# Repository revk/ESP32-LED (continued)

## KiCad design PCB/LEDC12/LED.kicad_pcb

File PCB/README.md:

# PCBs

Various PCBs designed for use with LED code.

## Trademark

This is an open source project, but bear in mind you cannot sell boards bearing the Andrews & Arnold Ltd name, the A&A logo, the registered trademark AJK logo, or the GS1 allocated EANs assigned to Andrews & Arnold Ltd.

## Coaster

Coaster board

## LEDA

USB-A board

## LEDC

USB-C board

## LEDX

Non USB board

## LEDR

USB-C uber board

## LEDx2

USB-C dual LED board

## LED32

88 LED disk, 32mm diameter

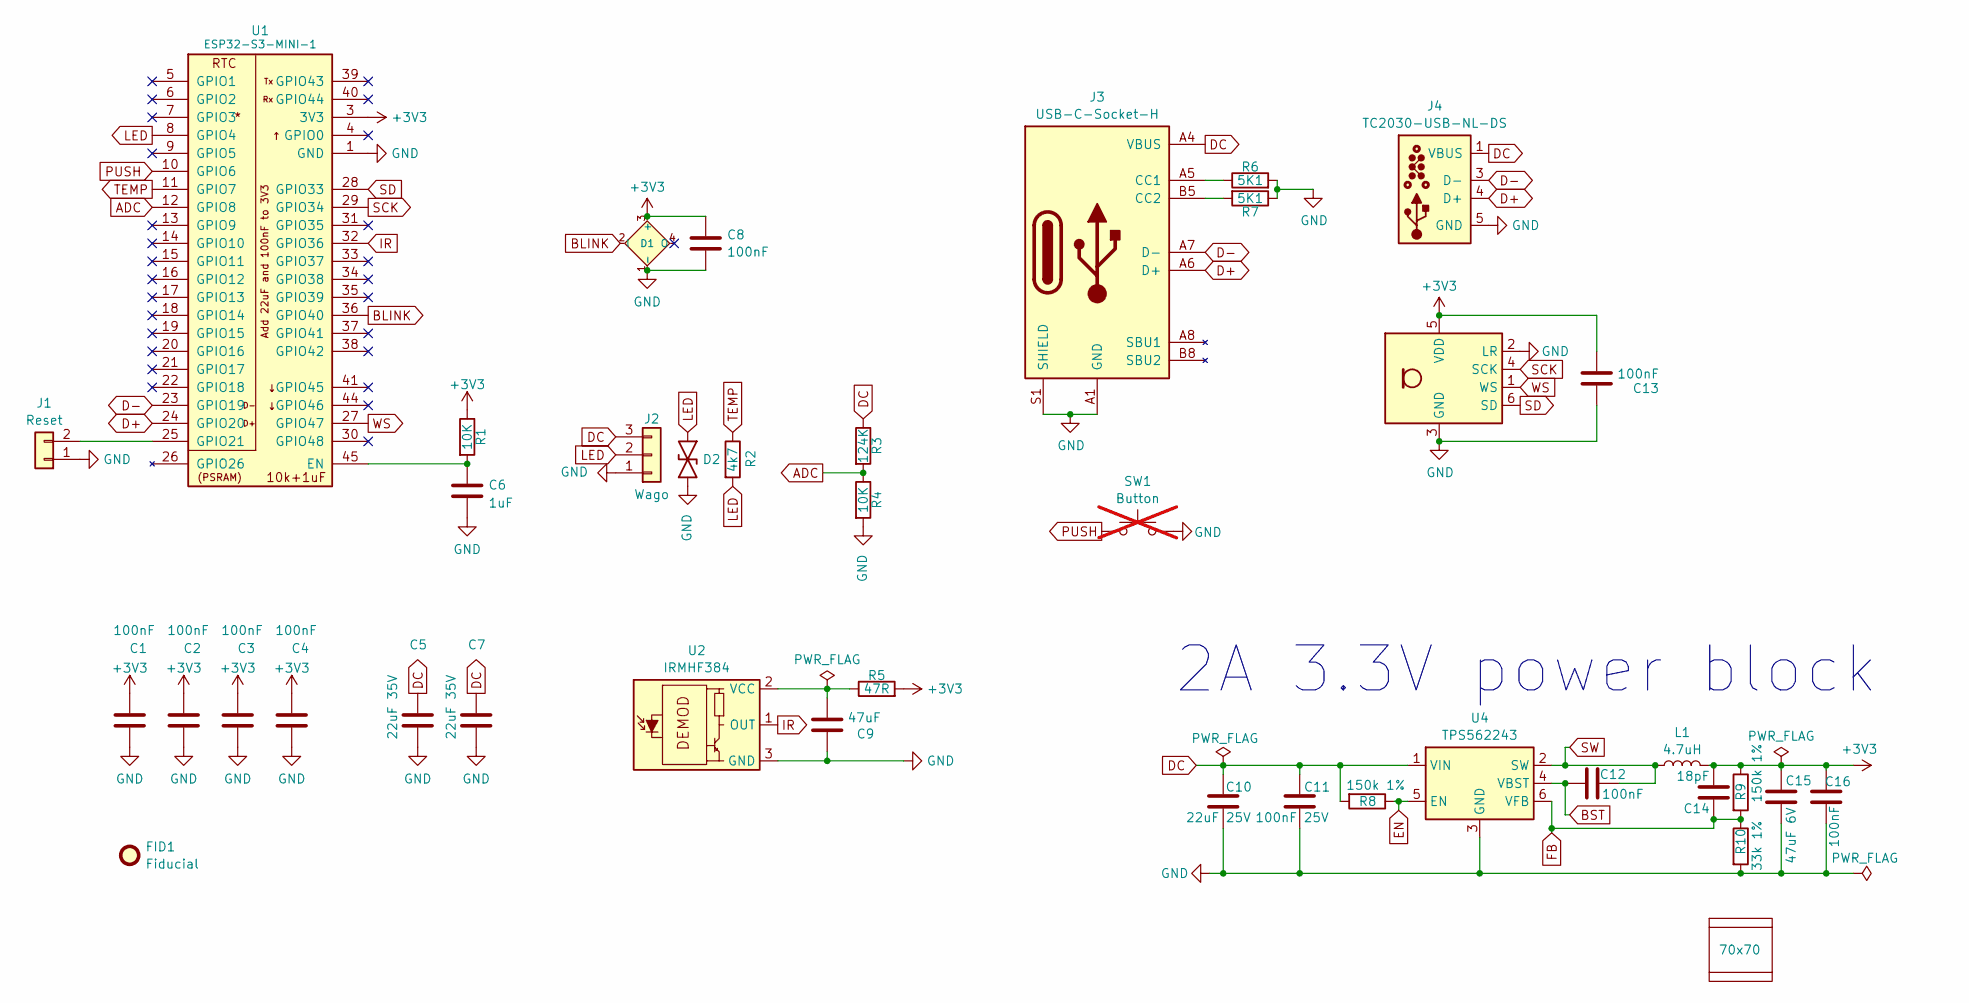
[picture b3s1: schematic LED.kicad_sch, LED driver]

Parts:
C1, C2, C3, C4, C8, C13: 100nF; C_0201
C5, C7: 22uF 35V; C_0805; MPN C6119901
C6: 1uF; C_0201
C9: 47uF; C_0603
C10: 22uF 25V; C_0805; MPN C45783
C11: 100nF 25V; C_0402; MPN C56392
C12, C16: 100nF; C_0201; MPN C76934
C14: 18pF; C_0201; MPN C62164
C15: 47uF 6V; C_0805; MPN C16780
D1: XL-1010RGBC-WS2812B; SMD1615; MPN C5349954
D2: DFN1006-2L; MPN C5137770
FID1: Fiducial; Fiducial_1mm_Mask2mm
J1: Reset; AA-Pad
J2: Wago; WAGO-2060-453-998-404; MPN C2765056
J3: USB-C-Socket-H; MPN C709357
J4: TC2030-USB-NL-DS; Tag-Connect_TC2030-IDC-NL_2x03_P1.27mm_Vertical
L1: 4.7uH; L_5x5; MPN C307876
PCB1: 70x70; PCB7070
R1, R4: 10K; R_0201; MPN C473048
R2: 4k7; R_0201; MPN C270346
R3: 124K; R_0201; MPN C423759
R5: 47R; R_0201; MPN C273279
R6, R7: 5K1; R_0201; MPN C274341
R8, R9: 150k 1%; R_0201; MPN C310173
R10: 33k 1%; R_0201; MPN C320835
SW1: Button; SW_Push_1P1T_NO_6x6mm; not fitted
U1: ESP32-S3-MINI-1; MPN C3013941
U2: IRMHF384; IR-SMD-4P,3.35x3.9mm; MPN C7280961
U3: ICS43434_MEMS_Mic; ICS43434_MEMS_Mic_Open; MPN C5656610
U4: TPS562243; SOT-563; MPN C42295941
V1, V2: VCUT70N

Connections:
+3V3: C1.1, C2.1, C3.1, C4.1, C8.1, C13.2, C14.2, C15.1, C16.2, D1.3 (+), L1.2, R1.1, R5.2, R9.1, U1.3 (3V3), U3.5 (VDD)
ADC: R3.2, R4.1, U1.12 (GPIO8)
BLINK: D1.2 (I), U1.36 (GPIO40)
BST: C12.1, U4.4 (VBST)
D+: J3.A6 (D+), J3.B6 (D+), J4.4 (D+), U1.24 (GPIO20)
D-: J3.A7 (D-), J3.B7 (D-), J4.2 (NC), J4.3 (D-), J4.6 (NC), U1.23 (GPIO19)
DC: C5.1, C7.1, C10.1, C11.1, J2.3, J3.A4 (VBUS), J3.A9 (VBUS), J3.B4 (VBUS), J3.B9 (VBUS), J4.1 (VBUS), R3.1, R8.2, U4.1 (VIN)
EN: R8.1, U4.5 (EN)
FB: C14.1, R9.2, R10.1, U4.6 (VFB)
GND: C1.2, C2.2, C3.2, C4.2, C5.2, C6.2, C7.2, C8.2, C9.2, C10.2, C11.2, C13.1, C15.2, C16.1, D1.1 (-), D2.1, J1.1, J2.1, J3.A1 (GND), J3.A12 (GND), J3.B1 (GND), J3.B12 (GND), J3.S1 (SHIELD), J4.5 (GND), R4.2, R6.2, R7.1, R10.2, SW1.2, U1.1 (GND), U1.2 (GND), U1.42 (GND), U1.43 (GND), U1.46 (GND), U1.47 (GND), U1.48 (GND), U1.49 (GND), U1.50 (GND), U1.51 (GND), U1.52 (GND), U1.53 (GND), U1.54 (GND), U1.55 (GND), U1.56 (GND), U1.57 (GND), U1.58 (GND), U1.59 (GND), U1.60 (GND), U1.61 (GND), U1.62 (GND), U1.63 (GND), U1.64 (GND), U1.65 (GND), U2.3 (GND), U2.4 (GND), U3.2 (LR), U3.3 (GND), U4.3 (GND)
IR: U1.32 (GPIO36), U2.1 (OUT)
LED: D2.2, J2.2, R2.2, U1.8 (GPIO4)
unnamed: J1.2, U1.25 (GPIO21)
unnamed: J3.A5 (CC1), R6.1
unnamed: J3.B5 (CC2), R7.2
unnamed: C6.1, R1.2, U1.45 (EN)
unnamed: C9.1, R5.1, U2.2 (VCC)
PUSH: SW1.1, U1.10 (GPIO6)
SCK: U1.29 (GPIO34), U3.4 (SCK)
SD: U1.28 (GPIO33), U3.6 (SD)
SW: C12.2, L1.1, U4.2 (SW)
TEMP: R2.1, U1.11 (GPIO7)
WS: U1.27 (GPIO47), U3.1 (WS)

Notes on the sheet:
2A 3.3V power block

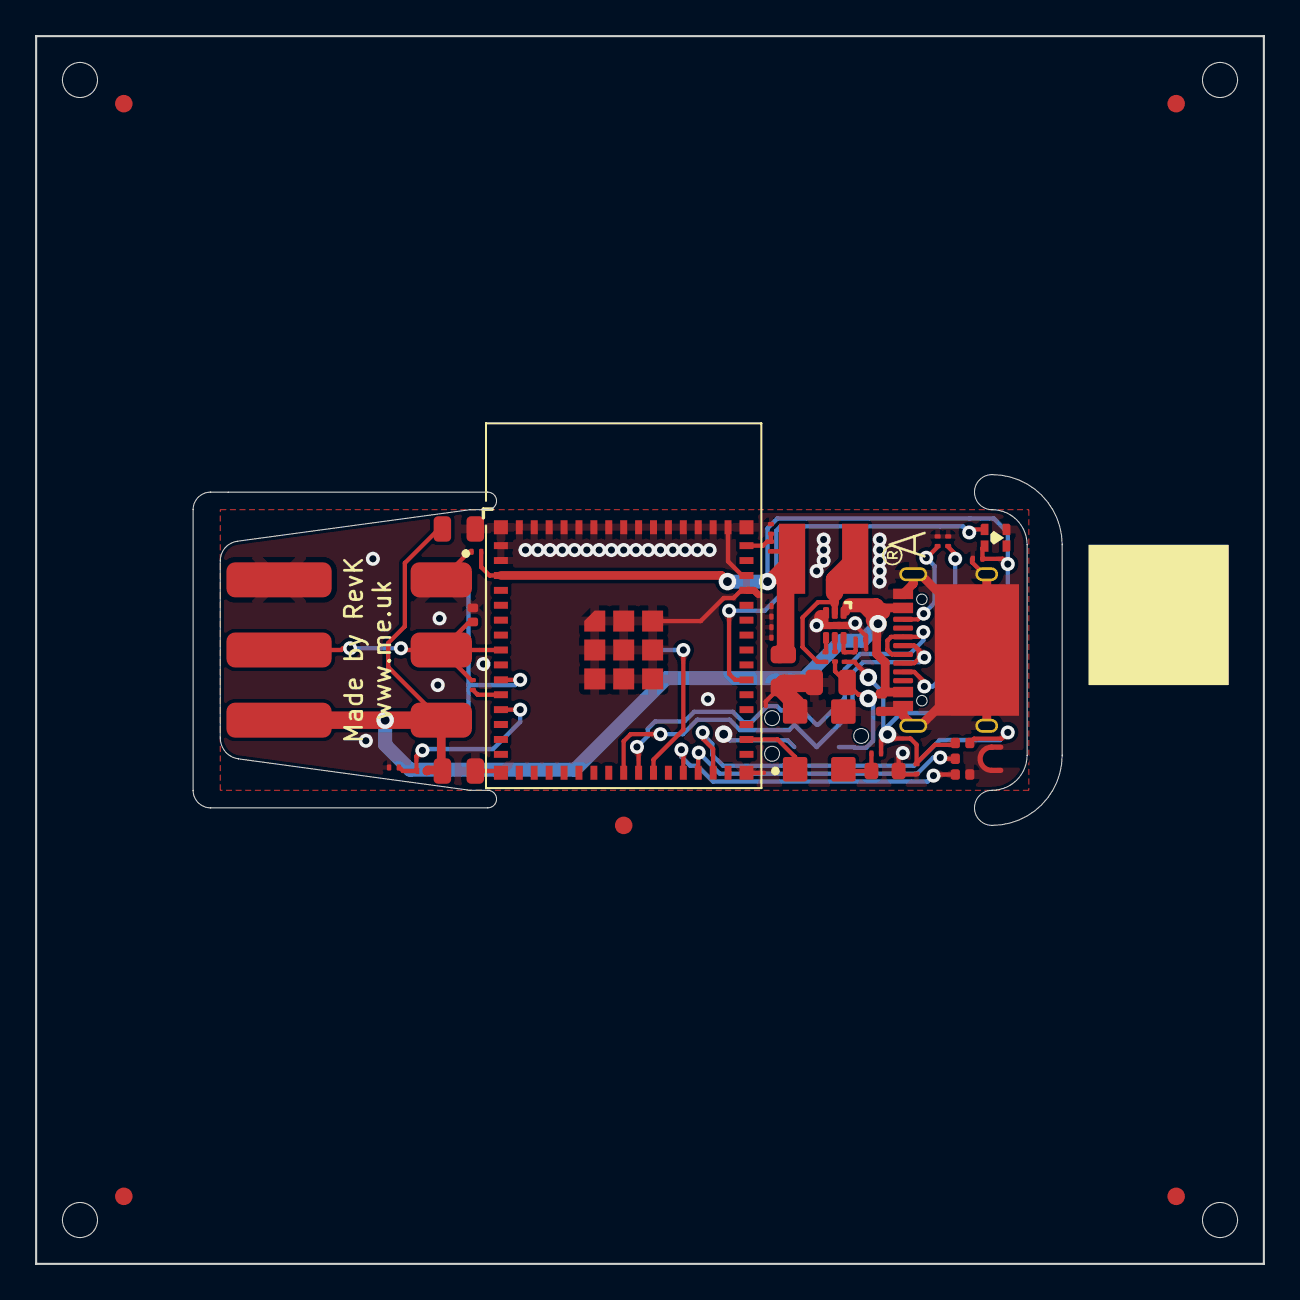
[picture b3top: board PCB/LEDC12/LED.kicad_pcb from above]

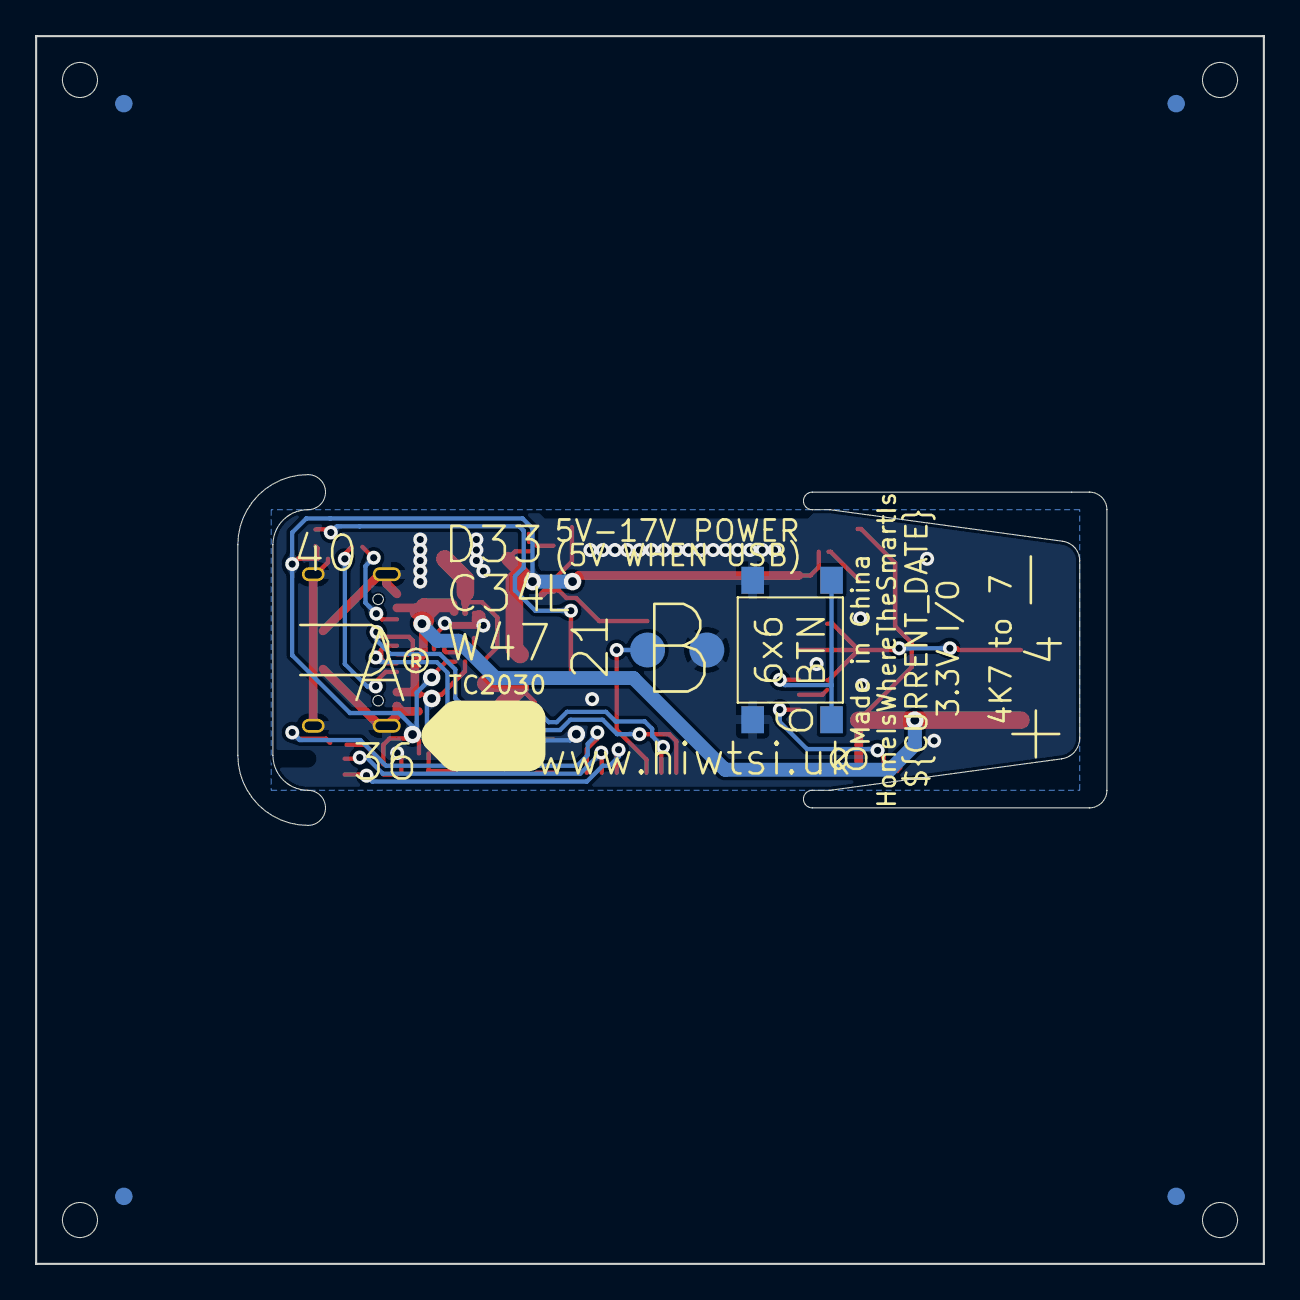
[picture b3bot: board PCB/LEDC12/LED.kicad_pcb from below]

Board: 2 copper layers, 70.0 x 70.0 mm, 42 parts (3 on the bottom side), 23 nets.

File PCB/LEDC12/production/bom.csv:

Designator,Footprint,Quantity,Value,LCSC Part #
"C1, C13, C2, C3, C4, C8",C_0201,6,100nF,
C10,C_0805,1,22uF 25V,C45783
C11,C_0402,1,100nF 25V,C56392
"C12, C16",C_0201,2,100nF,C76934
C14,C_0201,1,18pF,C62164
C15,C_0805,1,47uF 6V,C16780
"C5, C7",C_0805,2,22uF 35V,C6119901
C6,C_0201,1,1uF,
C9,C_0603,1,47uF,
D1,SMD1615,1,XL-1010RGBC-WS2812B,C5349954
D2,DFN1006-2L,1,~,C5137770
J2,WAGO-2060-453-998-404,1,Wago,C2765056
J3,USB-C-Socket-H,1,USB-C-Socket-H,C709357
L1,L_5x5,1,4.7uH,C307876
"R1, R4",R_0201,2,10K,C473048
R10,R_0201,1,33k 1%,C320835
R2,R_0201,1,4k7,C270346
R3,R_0201,1,124K,C423759
R5,R_0201,1,47R,C273279
"R6, R7",R_0201,2,5K1,C274341
"R8, R9",R_0201,2,150k 1%,C310173
U1,ESP32-S3-MINI-1,1,ESP32-S3-MINI-1-N4R2,C3013941
U2,"IR-SMD-4P,3.35x3.9mm",1,IRMHF384,C7280961
U3,ICS43434_MEMS_Mic_Open,1,ICS43434_MEMS_Mic,C5656610
U4,SOT-563,1,TPS562243,C42295941

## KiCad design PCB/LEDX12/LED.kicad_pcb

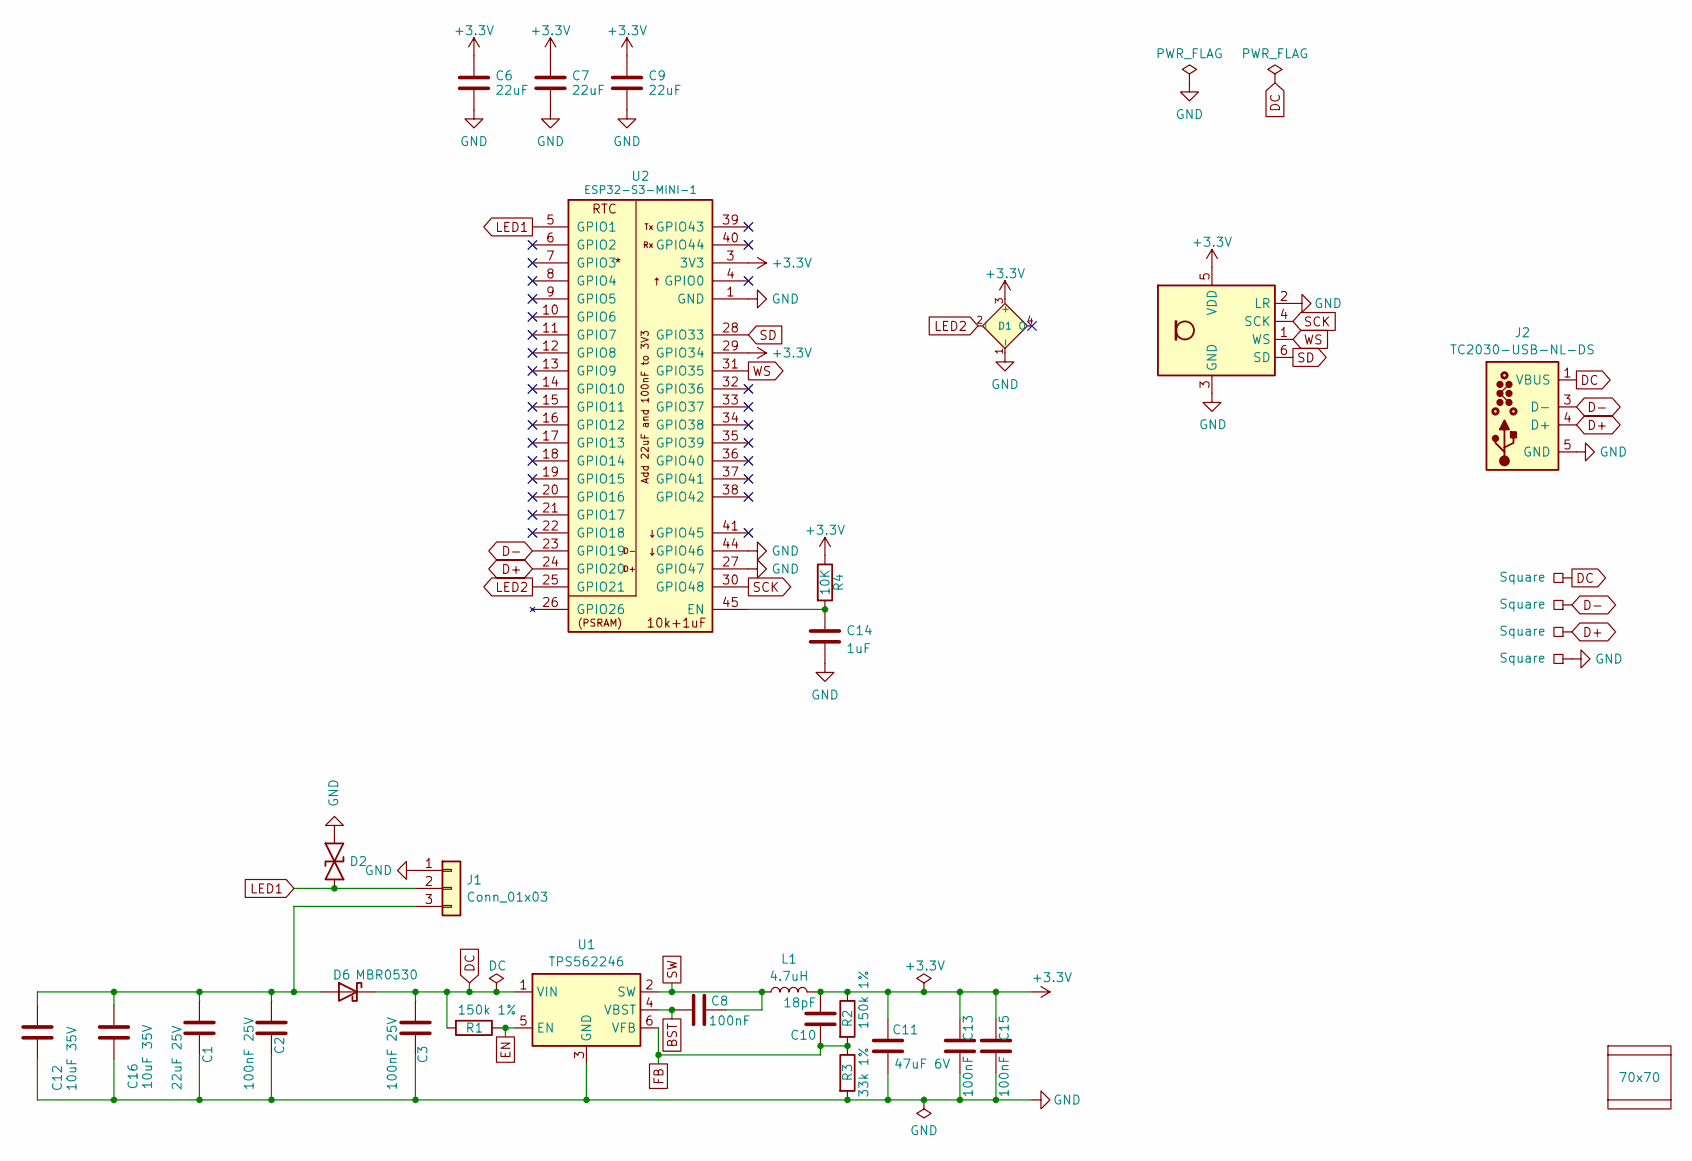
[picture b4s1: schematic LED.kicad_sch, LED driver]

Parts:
C1: 22uF 25V; C_0805; MPN C45783
C2, C3: 100nF 25V; C_0402; MPN C56392
C6, C7, C9: 22uF; C_0402
C8, C13, C15: 100nF; C_0201; MPN C76934
C10: 18pF; C_0201; MPN C62164
C11: 47uF 6V; C_0805; MPN C16780
C12, C16: 10uF 35V; C_0603; MPN C194427
C14: 1uF; C_0201
D1: XL-1010RGBC-WS2812B; SMD1615; MPN C5349954
D2: DFN1006-2L; MPN C5137770
D6: MBR0530; D_SOD-123; MPN C5204746
J1: Conn_01x03; WAGO-2060-453-998-404-O; MPN C2765056
J2: TC2030-USB-NL-DS; Tag-Connect_TC2030-IDC-NL_2x03_P1.27mm_Vertical
L1: 4.7uH; L_5x5; MPN C307876
P1, P2, P3, P4: Square; PAD-2mm
PCB1: 70x70; PCB7070
R1, R2: 150k 1%; R_0201; MPN C310173
R3: 33k 1%; R_0201; MPN C320835
R4: 10K; R_0201; MPN C473048
U1: TPS562246; SOT-563; MPN C41833479
U2: ESP32-S3-MINI-1; MPN C3013941
U3: ICS43434_MEMS_Mic; ICS43434_MEMS_Mic_Open; MPN C5656610
V1, V2: 70; VCUT70N

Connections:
+3.3V: C6.1, C7.1, C9.1, C10.2, C11.1, C13.2, C15.2, D1.3 (+), L1.2, R2.1, R4.1, U2.3 (3V3), U2.29 (GPIO34), U3.5 (VDD)
BST: C8.1, U1.4 (VBST)
D+: J2.4 (D+), P3.1, U2.24 (GPIO20)
D-: J2.2 (NC), J2.3 (D-), J2.6 (NC), P2.1, U2.23 (GPIO19)
DC: C3.1, D6.1 (K), J2.1 (VBUS), P1.1, R1.2, U1.1 (VIN)
EN: R1.1, U1.5 (EN)
FB: C10.1, R2.2, R3.1, U1.6 (VFB)
GND: C1.2, C2.2, C3.2, C6.2, C7.2, C9.2, C11.2, C12.2, C13.1, C14.2, C15.1, C16.2, D1.1 (-), D2.1, J1.1, J2.5 (GND), P4.1, R3.2, U1.3 (GND), U2.1 (GND), U2.2 (GND), U2.27 (GPIO47), U2.42 (GND), U2.43 (GND), U2.44 (GPIO46), U2.46 (GND), U2.47 (GND), U2.48 (GND), U2.49 (GND), U2.50 (GND), U2.51 (GND), U2.52 (GND), U2.53 (GND), U2.54 (GND), U2.55 (GND), U2.56 (GND), U2.57 (GND), U2.58 (GND), U2.59 (GND), U2.60 (GND), U2.61 (GND), U2.62 (GND), U2.63 (GND), U2.64 (GND), U2.65 (GND), U3.2 (LR), U3.3 (GND)
LED1: D2.2, J1.2, U2.5 (GPIO1)
LED2: D1.2 (I), U2.25 (GPIO21)
unnamed: C1.1, C2.1, C12.1, C16.1, D6.2 (A), J1.3
unnamed: C14.1, R4.2, U2.45 (EN)
SCK: U2.30 (GPIO48), U3.4 (SCK)
SD: U2.28 (GPIO33), U3.6 (SD)
SW: C8.2, L1.1, U1.2 (SW)
WS: U2.31 (GPIO35), U3.1 (WS)

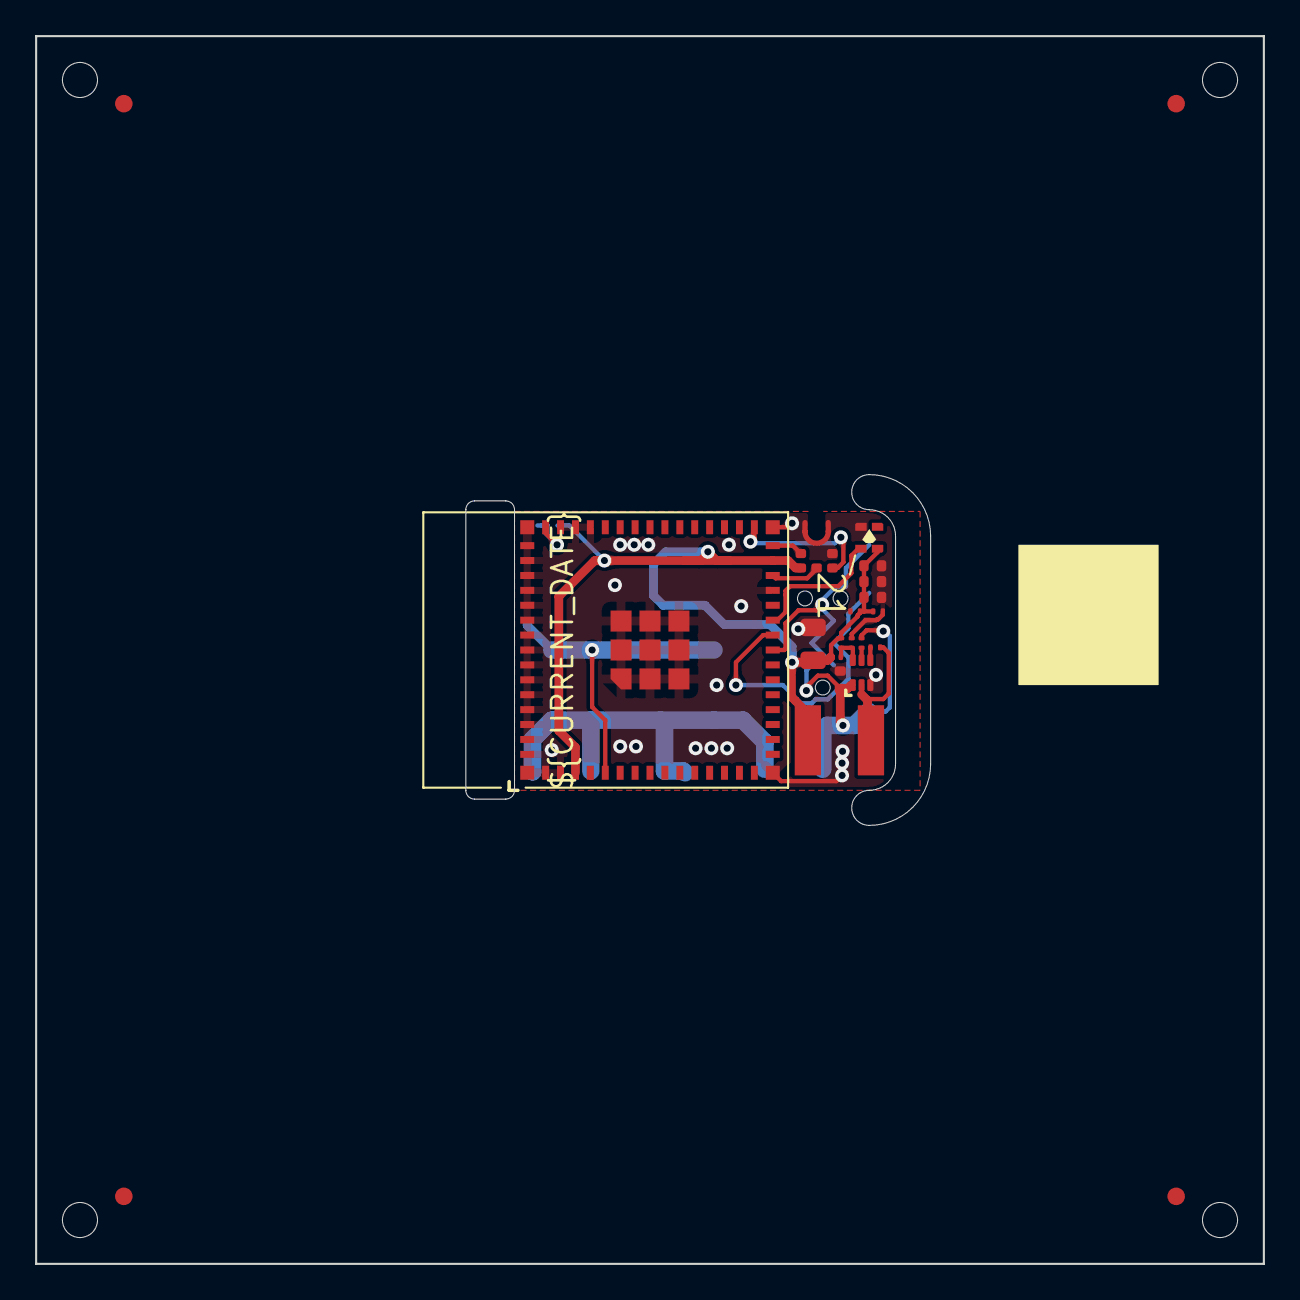
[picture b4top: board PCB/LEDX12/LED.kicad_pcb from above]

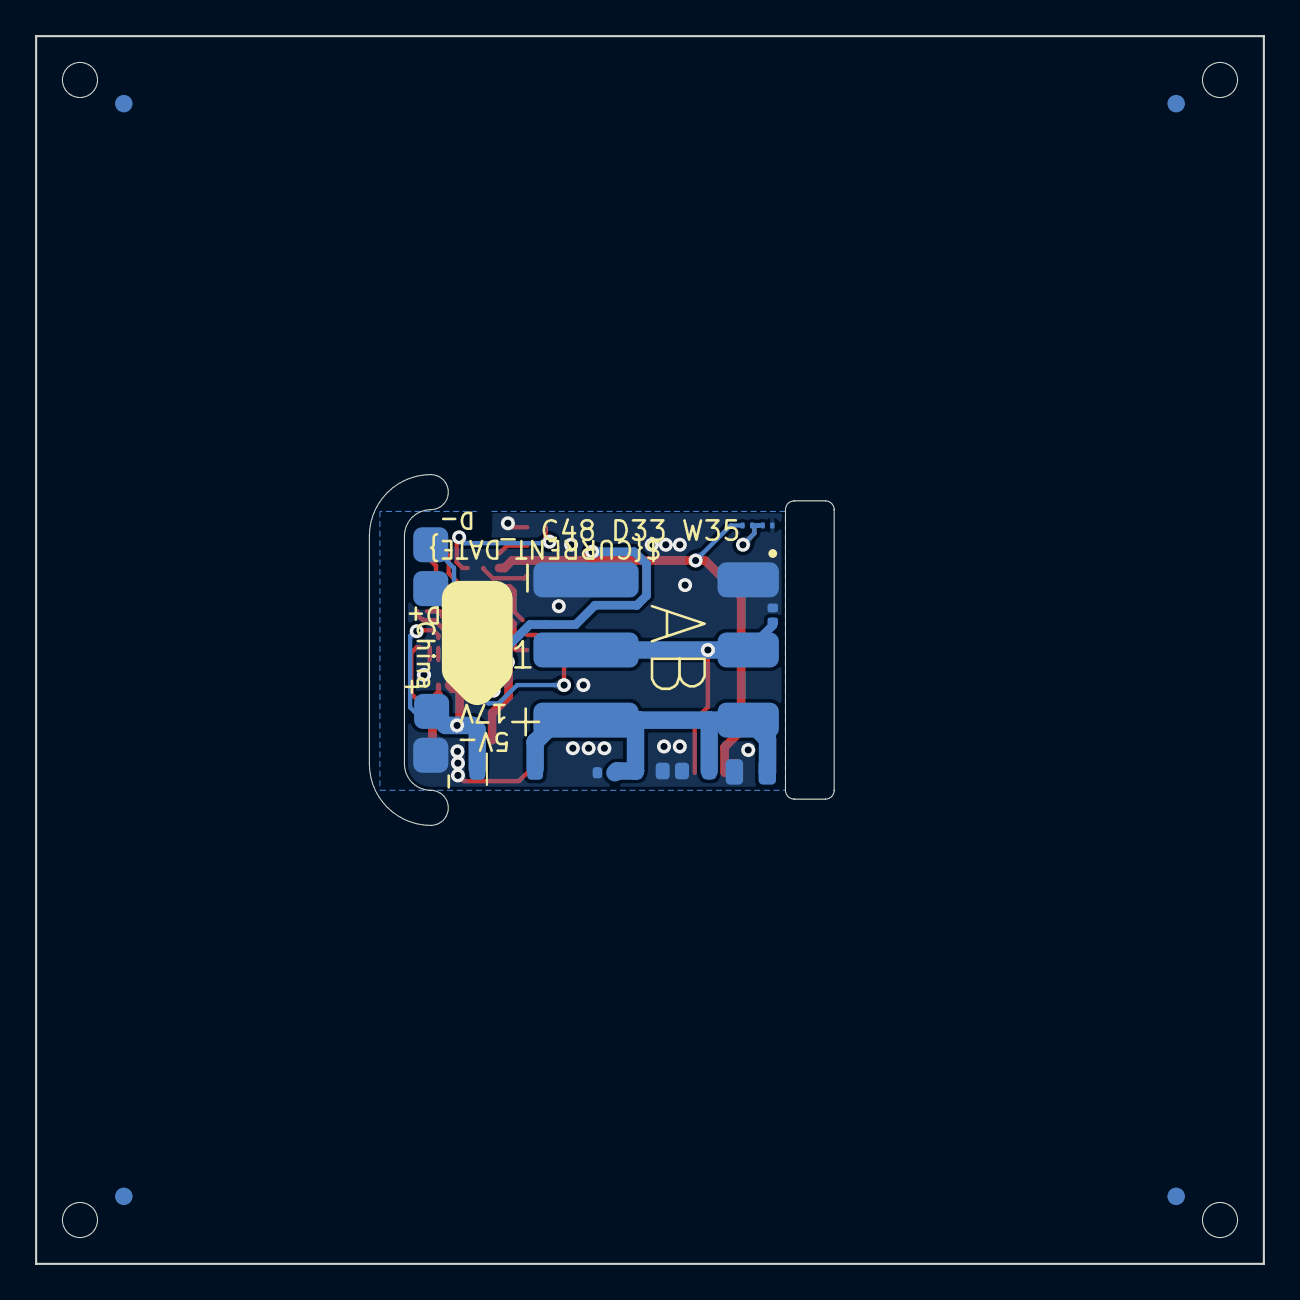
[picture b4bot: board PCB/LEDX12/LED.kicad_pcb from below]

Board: 2 copper layers, 70.0 x 70.0 mm, 34 parts (15 on the bottom side), 16 nets.

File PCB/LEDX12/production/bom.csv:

Designator,Footprint,Quantity,Value,LCSC Part #
C1,C_0805,1,22uF 25V,C45783
C10,C_0201,1,18pF,C62164
C11,C_0805,1,47uF 6V,C16780
"C12, C16",C_0603,2,10uF 35V,C194427
"C13, C15, C8",C_0201,3,100nF,C76934
C14,C_0201,1,1uF,
"C2, C3",C_0402,2,100nF 25V,C56392
"C6, C7, C9",C_0402,3,22uF,
D1,SMD1615,1,XL-1010RGBC-WS2812B,C5349954
D2,DFN1006-2L,1,~,C5137770
D6,D_SOD-123,1,MBR0530,C5204746
J1,WAGO-2060-453-998-404-O,1,Conn_01x03,C2765056
L1,L_5x5,1,4.7uH,C307876
"R1, R2",R_0201,2,150k 1%,C310173
R3,R_0201,1,33k 1%,C320835
R4,R_0201,1,10K,C473048
U1,SOT-563,1,TPS562246,C41833479
U2,ESP32-S3-MINI-1,1,ESP32-S3-MINI-1-N4R2,C3013941
U3,ICS43434_MEMS_Mic_Open,1,ICS43434_MEMS_Mic,C5656610

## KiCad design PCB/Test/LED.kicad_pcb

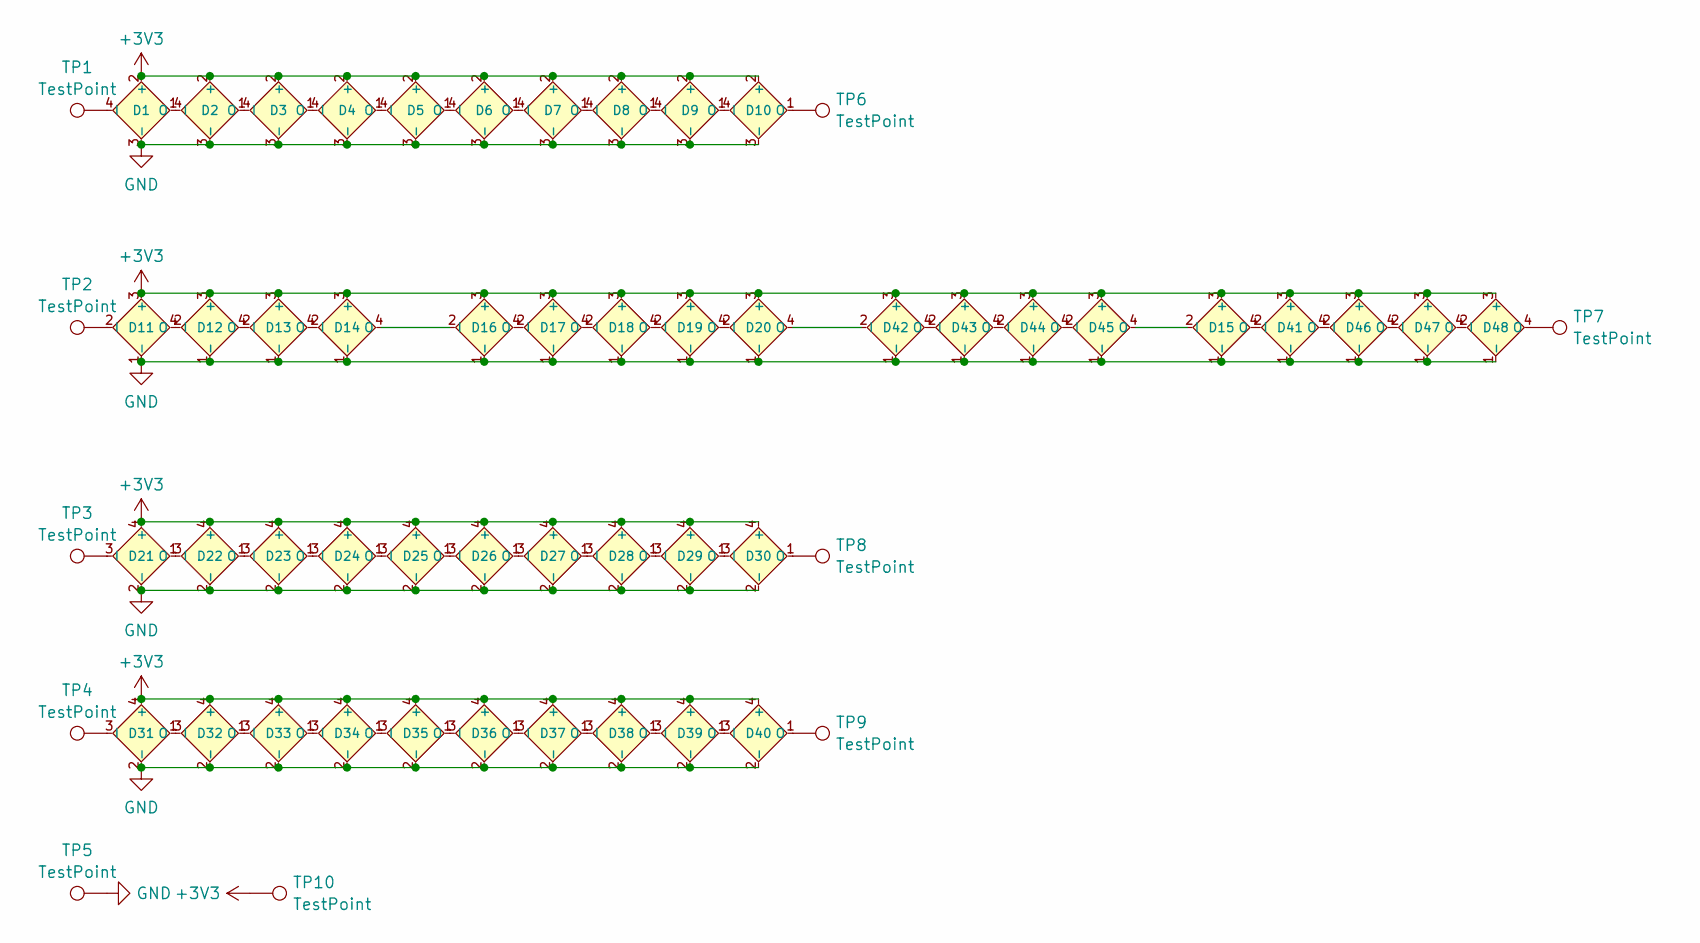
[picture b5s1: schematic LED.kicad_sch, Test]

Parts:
D1, D2, D3, D4, D5, D6, D7, D8, D9, D10: XL-1010RGBC-WS2812B; SMD1010; MPN C5349953
D11, D12, D13, D14, D15, D16, D17, D18, D19, D20, D41, D42, D43, D44, D45, D46, D47, D48: XL-1615RGBC-WS2812B; SMD1615; MPN C5349954
D21, D22, D23, D24, D25, D26, D27, D28, D29, D30, D31, D32, D33, D34, D35, D36, D37, D38, D39, D40: XL-2020RGBC-WS2812B; SMD2020; MPN C5349955
TP1, TP2, TP3, TP4, TP5, TP6, TP7, TP8, TP9, TP10: TestPoint; PAD-2mm

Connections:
+3V3: D1.2 (+), D2.2 (+), D3.2 (+), D4.2 (+), D5.2 (+), D6.2 (+), D7.2 (+), D8.2 (+), D9.2 (+), D10.2 (+), D11.3 (+), D12.3 (+), D13.3 (+), D14.3 (+), D15.3 (+), D16.3 (+), D17.3 (+), D18.3 (+), D19.3 (+), D20.3 (+), D21.4 (+), D22.4 (+), D23.4 (+), D24.4 (+), D25.4 (+), D26.4 (+), D27.4 (+), D28.4 (+), D29.4 (+), D30.4 (+), D31.4 (+), D32.4 (+), D33.4 (+), D34.4 (+), D35.4 (+), D36.4 (+), D37.4 (+), D38.4 (+), D39.4 (+), D40.4 (+), D41.3 (+), D42.3 (+), D43.3 (+), D44.3 (+), D45.3 (+), D46.3 (+), D47.3 (+), D48.3 (+), TP10.1
GND: D1.3 (-), D2.3 (-), D3.3 (-), D4.3 (-), D5.3 (-), D6.3 (-), D7.3 (-), D8.3 (-), D9.3 (-), D10.3 (-), D11.1 (-), D12.1 (-), D13.1 (-), D14.1 (-), D15.1 (-), D16.1 (-), D17.1 (-), D18.1 (-), D19.1 (-), D20.1 (-), D21.2 (-), D22.2 (-), D23.2 (-), D24.2 (-), D25.2 (-), D26.2 (-), D27.2 (-), D28.2 (-), D29.2 (-), D30.2 (-), D31.2 (-), D32.2 (-), D33.2 (-), D34.2 (-), D35.2 (-), D36.2 (-), D37.2 (-), D38.2 (-), D39.2 (-), D40.2 (-), D41.1 (-), D42.1 (-), D43.1 (-), D44.1 (-), D45.1 (-), D46.1 (-), D47.1 (-), D48.1 (-), TP5.1
unnamed: D1.4 (I), TP1.1
unnamed: D1.1 (O), D2.4 (I)
unnamed: D2.1 (O), D3.4 (I)
unnamed: D3.1 (O), D4.4 (I)
unnamed: D4.1 (O), D5.4 (I)
unnamed: D5.1 (O), D6.4 (I)
unnamed: D6.1 (O), D7.4 (I)
unnamed: D7.1 (O), D8.4 (I)
unnamed: D8.1 (O), D9.4 (I)
unnamed: D9.1 (O), D10.4 (I)
unnamed: D10.1 (O), TP6.1
unnamed: D11.2 (I), TP2.1
unnamed: D11.4 (O), D12.2 (I)
unnamed: D12.4 (O), D13.2 (I)
unnamed: D13.4 (O), D14.2 (I)
unnamed: D14.4 (O), D16.2 (I)
unnamed: D15.2 (I), D45.4 (O)
unnamed: D15.4 (O), D41.2 (I)
unnamed: D16.4 (O), D17.2 (I)
unnamed: D17.4 (O), D18.2 (I)
unnamed: D18.4 (O), D19.2 (I)
unnamed: D19.4 (O), D20.2 (I)
unnamed: D20.4 (O), D42.2 (I)
unnamed: D21.3 (I), TP3.1
unnamed: D21.1 (O), D22.3 (I)
unnamed: D22.1 (O), D23.3 (I)
unnamed: D23.1 (O), D24.3 (I)
unnamed: D24.1 (O), D25.3 (I)
unnamed: D25.1 (O), D26.3 (I)
unnamed: D26.1 (O), D27.3 (I)
unnamed: D27.1 (O), D28.3 (I)
unnamed: D28.1 (O), D29.3 (I)
unnamed: D29.1 (O), D30.3 (I)
unnamed: D30.1 (O), TP8.1
unnamed: D31.3 (I), TP4.1
unnamed: D31.1 (O), D32.3 (I)
unnamed: D32.1 (O), D33.3 (I)
unnamed: D33.1 (O), D34.3 (I)
unnamed: D34.1 (O), D35.3 (I)
unnamed: D35.1 (O), D36.3 (I)
unnamed: D36.1 (O), D37.3 (I)
unnamed: D37.1 (O), D38.3 (I)
unnamed: D38.1 (O), D39.3 (I)
unnamed: D39.1 (O), D40.3 (I)
unnamed: D40.1 (O), TP9.1
unnamed: D41.4 (O), D46.2 (I)
unnamed: D42.4 (O), D43.2 (I)
unnamed: D43.4 (O), D44.2 (I)
unnamed: D44.4 (O), D45.2 (I)
unnamed: D46.4 (O), D47.2 (I)
unnamed: D47.4 (O), D48.2 (I)
unnamed: D48.4 (O), TP7.1

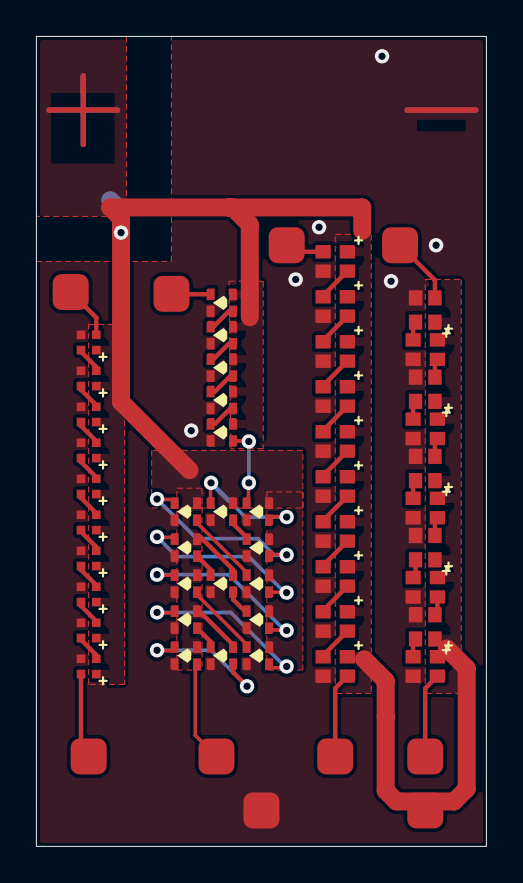
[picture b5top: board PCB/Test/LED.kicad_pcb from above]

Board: 2 copper layers, 25.0 x 45.0 mm, 58 parts (0 on the bottom side), 54 nets.

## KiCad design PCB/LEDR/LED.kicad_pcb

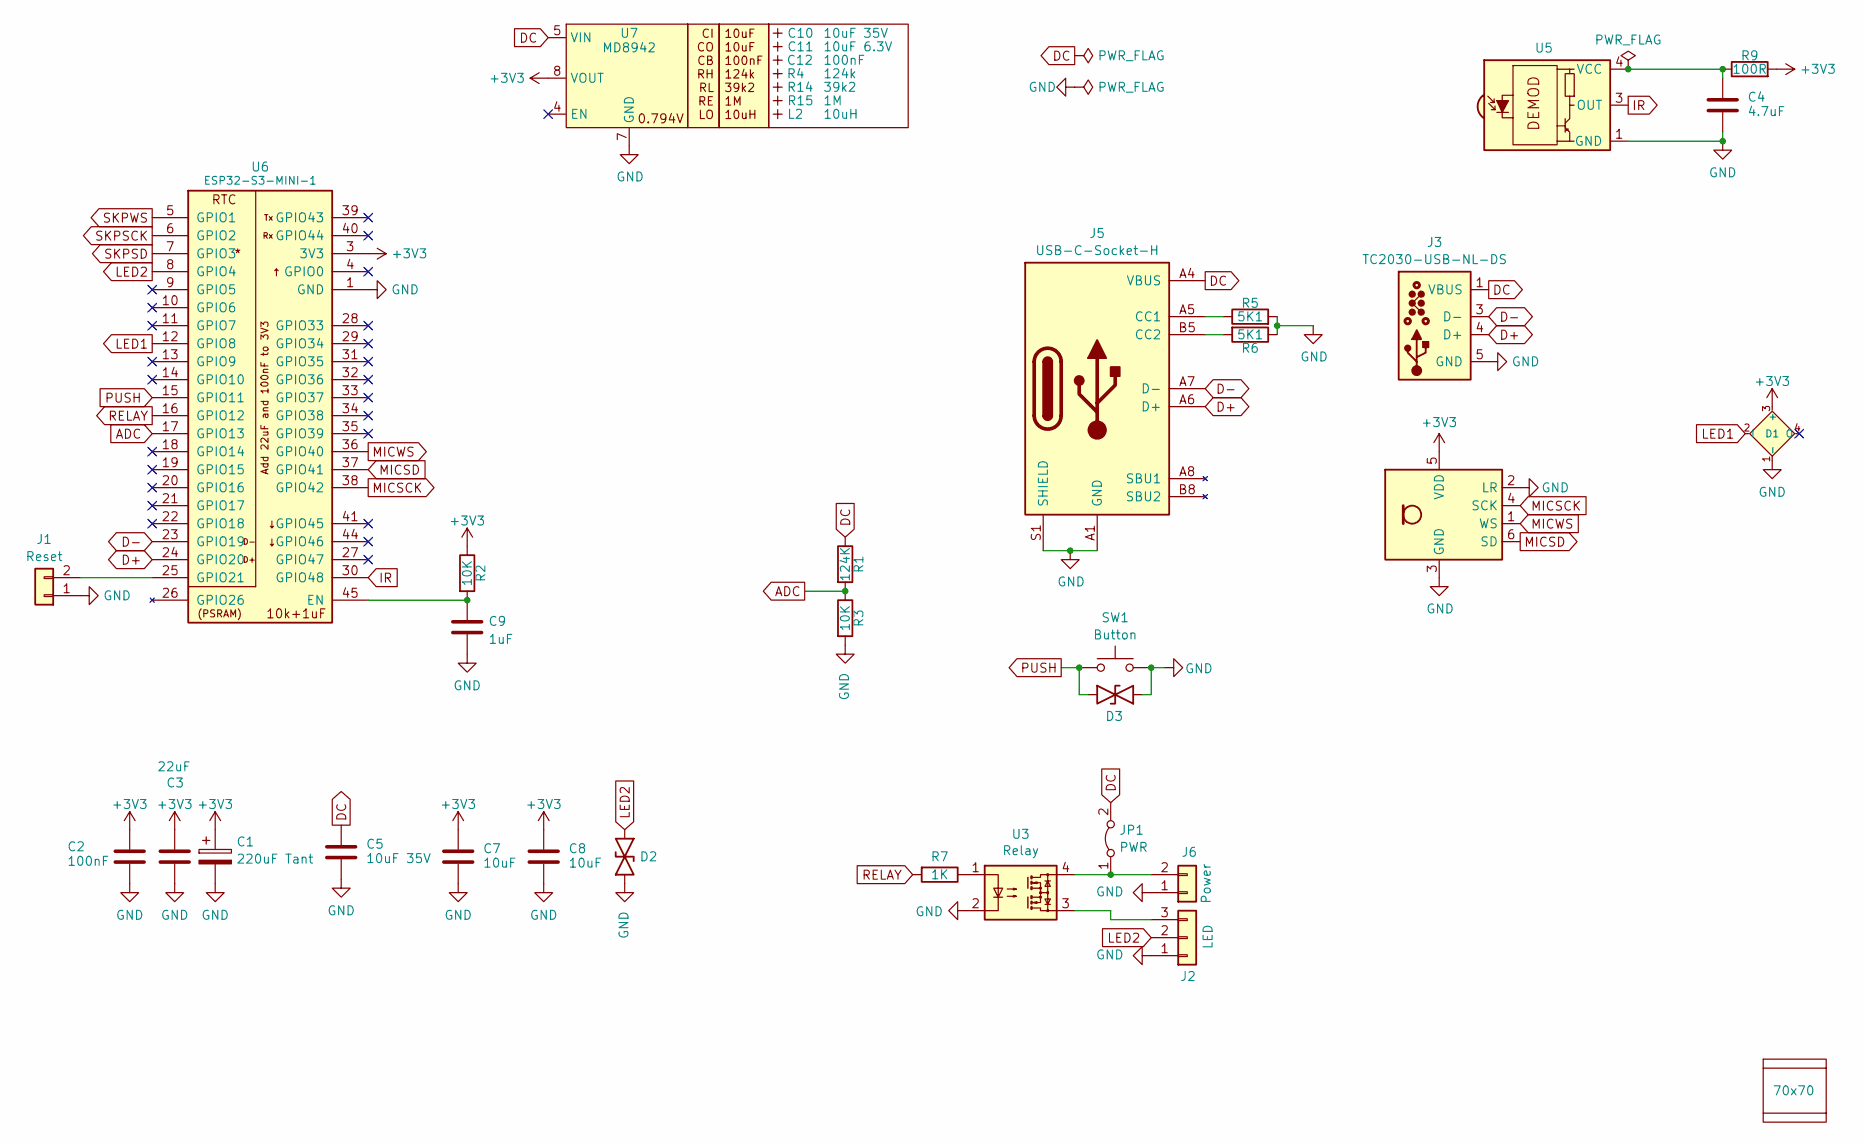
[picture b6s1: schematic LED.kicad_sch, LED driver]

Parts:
C1: 220uF Tant; CP_EIA-3528-21_Kemet-B; MPN C122649
C2: 100nF; C_0402
C3: 22uF; C_0603
C4: 4.7uF; C_0402; MPN C194427
C5: 10uF 35V; C_0603; MPN C194427
C7, C8: 10uF; C_0402; MPN C15525
C9: 1uF; C_0402
C10: 10uF 35V; C_0603_; MPN C194427
C11: 10uF 6.3V; C_0603_; MPN C1691
C12: 100nF; C_0603_
D1: XL-1010RGBC-WS2812B; SMD1615; MPN C5349954
D2, D3: DFN1006-2L; MPN C5137770
J1: Reset; AA-Pad
J2: LED; WAGO-2060-453-998-404; MPN C2765056
J3: TC2030-USB-NL-DS; Tag-Connect_TC2030-IDC-NL_2x03_P1.27mm_Vertical
J5: USB-C-Socket-H; MPN C709357
J6: Power; WAGO-2060-452-998-404; MPN C2765055
JP1: PWR; Pad_1206_0805_Bridged
L2: 10uH; L_4x4_
PCB1: 70x70; PCB7070
R1: 124K; R_0402
R2, R3: 10K; R_0402
R4: 124k; R_0402_
R5, R6: 5K1; R_0402
R7: 1K; R_0402
R9: 100R; R_0402
R14: 39k2; R_0402_
R15: 1M; R_0402_
SW1: Button; SW_Push_1P1T_NO_6x6mm
U1: ICS43434_MEMS_Mic; ICS43434_MEMS_Mic_Open; MPN C5656610
U3: Relay; SO-4_4.4x4.3mm_P2.54mm
U5: IRM-H638T/TR2; SMD-4P,4x5mm; MPN C91447
U6: ESP32-S3-MINI-1; MPN C3013941
U7: MD8942; SOT-23-6-MD8942; MPN C2684786
V1, V2: VCUT70N

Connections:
+3V3: C1.1, C2.1, C3.1, C7.1, C8.1, D1.3 (+), R2.1, R9.2, U1.5 (VDD), U6.3 (3V3), U7.8 (VOUT)
ADC: R1.2, R3.1, U6.17 (GPIO13)
D+: J3.4 (D+), J5.A6 (D+), J5.B6 (D+), U6.24 (GPIO20)
D-: J3.2 (NC), J3.3 (D-), J3.6 (NC), J5.A7 (D-), J5.B7 (D-), U6.23 (GPIO19)
DC: C5.1, J3.1 (VBUS), J5.A4 (VBUS), J5.A9 (VBUS), J5.B4 (VBUS), J5.B9 (VBUS), JP1.2 (B), R1.1, U7.5 (VIN)
GND: C1.2, C2.2, C3.2, C4.2, C5.2, C7.2, C8.2, C9.2, D1.1 (-), D2.1, D3.1, J1.1, J2.1, J3.5 (GND), J5.A1 (GND), J5.A12 (GND), J5.B1 (GND), J5.B12 (GND), J5.S1 (SHIELD), J6.1, R3.2, R5.2, R6.1, SW1.2, U1.2 (LR), U1.3 (GND), U3.2, U5.1 (GND), U5.2 (GND), U6.1 (GND), U6.2 (GND), U6.42 (GND), U6.43 (GND), U6.46 (GND), U6.47 (GND), U6.48 (GND), U6.49 (GND), U6.50 (GND), U6.51 (GND), U6.52 (GND), U6.53 (GND), U6.54 (GND), U6.55 (GND), U6.56 (GND), U6.57 (GND), U6.58 (GND), U6.59 (GND), U6.60 (GND), U6.61 (GND), U6.62 (GND), U6.63 (GND), U6.64 (GND), U6.65 (GND), U7.2 (GND), U7.7 (GND)
IR: U5.3 (OUT), U6.30 (GPIO48)
LED1: D1.2 (I), U6.12 (GPIO8)
LED2: D2.2, J2.2, U6.8 (GPIO4)
MICSCK: U1.4 (SCK), U6.38 (GPIO42)
MICSD: U1.6 (SD), U6.37 (GPIO41)
MICWS: U1.1 (WS), U6.36 (GPIO40)
unnamed: J1.2, U6.25 (GPIO21)
unnamed: J2.3, U3.3
unnamed: J5.A5 (CC1), R5.1
unnamed: J5.B5 (CC2), R6.2
unnamed: J6.2, JP1.1 (A), U3.4
unnamed: R7.1, U3.1
unnamed: C4.1, R9.1, U5.4 (VCC)
unnamed: C9.1, R2.2, U6.45 (EN)
PUSH: D3.2, SW1.1, U6.15 (GPIO11)
RELAY: R7.2, U6.16 (GPIO12)
SKPSCK: U6.6 (GPIO2)
SKPSD: U6.7 (GPIO3)
SKPWS: U6.5 (GPIO1)
